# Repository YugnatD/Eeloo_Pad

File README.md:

# Eeloo Pad
## A Kerbal Space Program Control Panel
A Open Source project to create a control panel for Kerbal Space Program. The goal is to create a control panel that can be used to control the game from a physical panel. The control panel will be able to control the game, and display information about the game.

## Features
* Control the game (Thrust, SAS, RCS, etc.)
* TODO

## Block Diagram
[Diagram](https://app.diagrams.net/#G1_EMb1VFjsUEVt7AdRK-4kCuMEsyWomvp)

## Schematic

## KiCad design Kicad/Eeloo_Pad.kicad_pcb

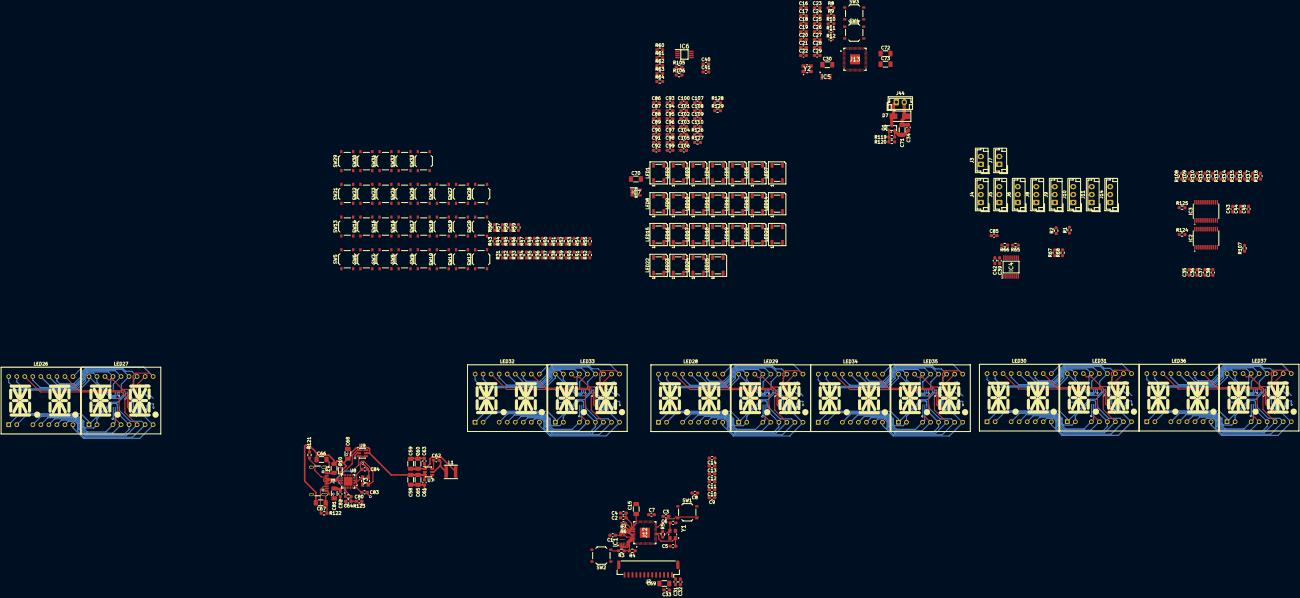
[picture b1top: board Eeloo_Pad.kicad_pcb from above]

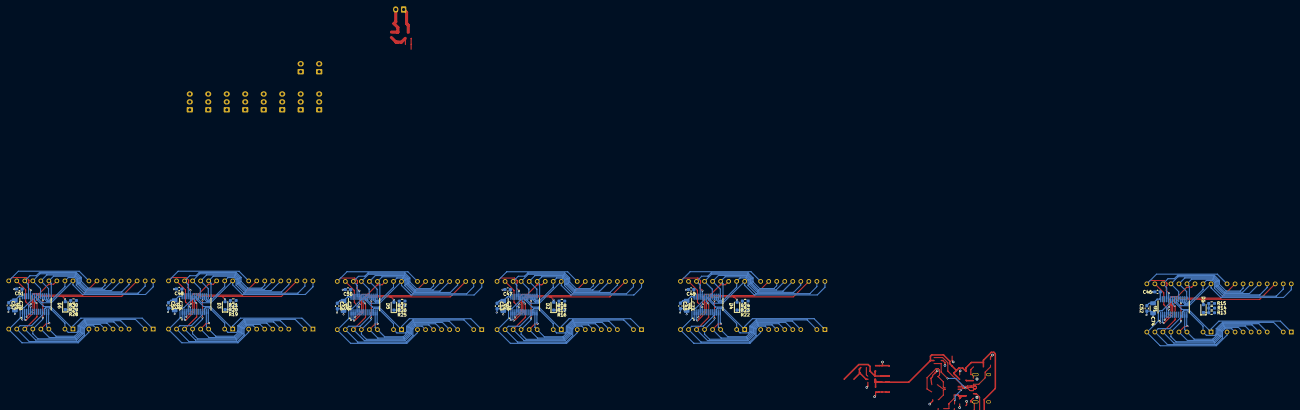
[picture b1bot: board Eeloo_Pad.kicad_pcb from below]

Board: 2 copper layers, 318 parts (48 on the bottom side), 265 nets.

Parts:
C1, C3, C4, C8, C9, C10, C11, C12, C13, C14, C16, C18, C19, C23, C24, C25, C26, C27, C28, C29, C31, C32, C33, C34, C35, C36, C37, C38, C39, C40, C41, C42, C43, C44, C45, C46, C47, C48, C49, C50, C51, C52, C53, C54, C55, C56, C57, C64, C82, C85, C86, C87, C88, C89, C90, C91, C92, C93, C94, C95, C96, C97, C98, C99, C100, C101, C102, C103, C104, C105, C106, C107, C108, C109, C110: 100n; C_0603_1608Metric_Pad1.08x0.95mm_HandSolder
C2, C7, C17, C22, C80: 1u; C_0603_1608Metric_Pad1.08x0.95mm_HandSolder
C5, C6, C20, C21, C83, C84: 15p; C_0603_1608Metric_Pad1.08x0.95mm_HandSolder
C15, C30, C81: 10u; C_1206_3216Metric_Pad1.33x1.80mm_HandSolder
C58, C59, C60, C65, C66, C67, C68, C69, C70, C71, C72, C73, C74, C75, C76, C77, C78, C79: 22uF; C_1206_3216Metric_Pad1.33x1.80mm_HandSolder
C61, C62, C63: 100nF; C_0603_1608Metric_Pad1.08x0.95mm_HandSolder
D1, D2, D3, D4, D5, D6: SD103AWS; D_SOD-323_HandSoldering
D7: SS34; D_SMA
D10: ESD5Zxx; D_SOD-523
F1: 1.5A; Fuse_1206_3216Metric
IC1, IC5: W25Q16JVUXIQ_TR; SON50P300X200X60-9N
IC2, IC3: PCA9535PW; TSSOP-24_4.4x7.8mm_P0.65mm
IC4: ADS7830IPWR; SOP65P640X120-16N
IC6: TCA9617ADGKR; SOP65P490X110-8N
IC7: SN74AHCT1G125DBVR; SOT95P280X145-5N
J1: USB_C_Receptacle_USB2.0_16P; USB_C_Receptacle_HCTL_HC-TYPE-C-16P-01A
J2: Conn_01x13; JST_GH_SM13B-GHS-TB_1x13-1MP_P1.25mm_Horizontal
J3, J7, J44: Conn_01x02_Pin; JST_EH_B2B-EH-A_1x02_P2.50mm_Vertical
J4, J5, J6, J8, J9, J10, J11, J14: Conn_01x03_Pin; JST_EH_B3B-EH-A_1x03_P2.50mm_Vertical
J12, J13: SC0914_13_; SC091413
L1: 3.9uH; L_Sunlord_SWPA4030S
LED1, LED2, LED3, LED4, LED5, LED6, LED7, LED8, LED9, LED10, LED11, LED12, LED13, LED14, LED15, LED16, LED17, LED18, LED19, LED20, LED21, LED22, LED23, LED24, LED25: XL-5050RGBC-WS2812B; LED_WS2812B_PLCC4_5.0x5.0mm_P3.2mm
LED26, LED27, LED28, LED29, LED30, LED31, LED32, LED33, LED34, LED35, LED36, LED37: FJ5241AH; LED-SEG-TH_18P-L25.2-W21.1-P2.54-LS15.2-BL
Q1: AO3400A; SOT-23
R1, R2, R31, R32, R33, R34, R35, R36, R37, R38, R39, R40, R41, R42, R43, R44, R45, R46, R47, R48, R49, R50, R51, R52, R53, R54, R55, R56, R57, R58, R59, R62, R65, R66, R67, R68, R107, R108, R109, R110, R111, R112, R113, R114, R115, R116, R117, R118, R119, R123, R124, R125, R127, R128, R129: 10k; R_0603_1608Metric_Pad0.98x0.95mm_HandSolder
R3, R5, R8, R10: 1k; R_0603_1608Metric_Pad0.98x0.95mm_HandSolder
R4, R9: NC; R_0603_1608Metric_Pad0.98x0.95mm_HandSolder
R6, R7, R11, R12: 27.4; R_0402_1005Metric_Pad0.72x0.64mm_HandSolder
R13, R14, R15, R16, R17, R18, R19, R20, R21, R22, R23, R24, R25, R26, R27, R28, R29, R30: 39k; R_0603_1608Metric_Pad0.98x0.95mm_HandSolder
R60, R61, R63, R64, R105, R106: 4k7; R_0603_1608Metric_Pad0.98x0.95mm_HandSolder
R120: 100; R_0603_1608Metric_Pad0.98x0.95mm_HandSolder
R121, R122: 5.1k; R_0603_1608Metric_Pad0.98x0.95mm_HandSolder
R126: 330; R_0603_1608Metric_Pad0.98x0.95mm_HandSolder
SW1, SW2, SW3, SW4, SW5, SW6, SW7, SW8, SW9, SW10, SW11, SW12, SW13, SW14, SW15, SW16, SW17, SW18, SW19, SW20, SW21, SW22, SW23, SW24, SW25, SW26, SW27, SW28, SW29, SW30, SW31, SW32, SW33: SW_Push; SW_Push_1P1T_XKB_TS-1187A
U1, U2, U3, U4, U5, U6: HT16K33A-28SSOP; SOP63P600X175-28N
U7: AP63203WU; TSOT-23-6
U8: CH334F; QFN-24-1EP_4x4mm_P0.5mm_EP2.7x2.7mm
U9: USBLC6-2SC6; SOT-23-6
Y1, Y2: ABM8-272-T3; ABM8272T3
Y3: 12MHz; ABM8272T3

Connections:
+3.3V: C1.1, C7.1, C8.1, C9.1, C10.1, C11.1, C12.1, C13.1, C14.1, C15.1, C16.1, C22.1, C23.1, C24.1, C25.1, C26.1, C27.1, C28.1, C29.1, C30.1, C31.1, C32.1, C33.1, C35.1, C36.1, C37.1, C38.1, C39.1, C40.1, C42.1, C59.1, C60.1, C63.1, C69.1, C72.1, C73.1, C85.1, IC1.8 (VCC), IC2.24 (VCC), IC3.24 (VCC), IC4.10 (REFIN/REFOUT), IC4.16 (+VDD), IC5.8 (VCC), IC6.1 (VCC(A)), J2.1, J4.1, J5.1, J6.1, J8.1, J9.1, J10.1, J11.1, J12.1 (IOVDD_1), J12.10 (IOVDD_2), J12.22 (IOVDD_3), J12.33 (IOVDD_4), J12.42 (IOVDD_5), J12.43 (ADC_AVDD), J12.44 (VREG_VIN), J12.48 (USB_VDD), J12.49 (IOVDD_6), J13.1 (IOVDD_1), J13.10 (IOVDD_2), J13.22 (IOVDD_3), J13.33 (IOVDD_4), J13.42 (IOVDD_5), J13.43 (ADC_AVDD), J13.44 (VREG_VIN), J13.48 (USB_VDD), J13.49 (IOVDD_6), J14.1, L1.2, R1.2, R2.2, R4.2, R9.2, R31.1, R32.1, R33.1, R34.1, R35.1, R36.1, R37.1, R38.1, R39.1, R40.1, R41.1, R42.1, R43.1, R44.1, R45.1, R46.1, R47.1, R48.1, R49.1, R50.1, R51.1, R52.1, R53.1, R54.1, R55.1, R56.1, R57.1, R58.1, R59.1, R63.1, R64.1, R65.1, R67.1, R105.1, R106.1, R107.1, R109.1, R111.1, R113.1, R115.1, R117.1, R124.1, R125.1, U7.1 (FB)
/CC1: J1.A5 (CC1), R121.1
/CC2: J1.B5 (CC2), R122.1
/HUB_OVCUR: R128.2, U8.1 (~OVCUR)
/HUB_PSELF: R129.1, U8.18 (PSELF)
/HUB_RESET: R123.2, U8.16 (~RESET/CDP)
/HUB_V33: C64.1, C80.1, R123.1, R128.1, U8.20 (VDD33_{LDO})
/USB1_DM: R7.2, U8.11 (DM1-)
/USB1_DP: R6.2, U8.12 (DP1+)
/USB2_DM: R12.2, U8.9 (DM2-)
/USB2_DP: R11.2, U8.10 (DP2+)
/USB_DM: J1.A7 (D-), J1.B7 (D-), U8.14 (DMU-), U9.1 (I/O1), U9.6 (I/O1)
/USB_DP: J1.A6 (D+), J1.B6 (D+), U8.15 (DPU+), U9.3 (I/O2), U9.4 (I/O2)
/VBUS: C34.1, C41.1, C43.1, C44.1, C45.1, C46.1, C47.1, C48.1, C49.1, C50.1, C51.1, C52.1, C53.1, C54.1, C55.1, C56.1, C57.1, C58.1, C61.1, C65.1, C66.1, C67.1, C68.1, C70.1, C71.1, C74.1, C75.1, C76.1, C77.1, C78.1, C79.1, C81.1, C82.1, C86.1, C87.1, C88.1, C89.1, C90.1, C91.1, C92.1, C93.1, C94.1, C95.1, C96.1, C97.1, C98.1, C99.1, C100.1, C101.1, C102.1, C103.1, C104.1, C105.1, C106.1, C107.1, C108.1, C109.1, C110.1, D7.1 (K), D10.1 (K), F1.2, IC6.8 (VCC(B)), IC7.5 (VCC), J44.2, LED1.1 (VDD), LED2.1 (VDD), LED3.1 (VDD), LED4.1 (VDD), LED5.1 (VDD), LED6.1 (VDD), LED7.1 (VDD), LED8.1 (VDD), LED9.1 (VDD), LED10.1 (VDD), LED11.1 (VDD), LED12.1 (VDD), LED13.1 (VDD), LED14.1 (VDD), LED15.1 (VDD), LED16.1 (VDD), LED17.1 (VDD), LED18.1 (VDD), LED19.1 (VDD), LED20.1 (VDD), LED21.1 (VDD), LED22.1 (VDD), LED23.1 (VDD), LED24.1 (VDD), LED25.1 (VDD), R60.1, R61.1, R62.1, U1.28 (VDD), U2.28 (VDD), U3.28 (VDD), U4.28 (VDD), U5.28 (VDD), U6.28 (VDD), U7.2 (EN), U7.3 (IN), U8.19 (V5), U9.5 (VBUS)
/control_module/ANTINORMAL: IC3.7 (P03), R49.2, SW21.2
/control_module/ANTI_MANEUVER: IC3.14 (P11), R55.2, SW32.2
/control_module/ANTI_TARGET: IC3.11 (P07), R53.2, SW28.2
/control_module/BRAKE: IC2.19 (P16), R45.2, SW19.2
/control_module/CIBLE_ORBIT: IC3.15 (P12), R56.2, SW31.2
/control_module/CTRL0: IC2.6 (P02), R33.2, SW7.2
/control_module/CTRL1: IC2.7 (P03), R34.2, SW8.2
/control_module/CTRL2: IC2.8 (P04), R35.2, SW9.2
/control_module/CTRL3: IC2.9 (P05), R36.2, SW14.2
/control_module/CTRL4: IC2.10 (P06), R37.2, SW13.2
/control_module/CTRL5: IC2.11 (P07), R38.2, SW12.2
/control_module/CTRL6: IC2.13 (P10), R39.2, SW11.2
/control_module/CTRL7: IC2.14 (P11), R40.2, SW10.2
/control_module/CTRL8: IC2.15 (P12), R41.2, SW15.2
/control_module/CTRL9: IC2.16 (P13), R42.2, SW16.2
/control_module/EXT1: IC4.1 (CH0), J14.2
/control_module/GEAR: IC2.18 (P15), R44.2, SW18.2
/control_module/I2C0_SCL_33: IC2.22 (SCL), IC3.22 (SCL), IC4.14 (SCL), J13.7 (GPIO5), R105.2
/control_module/I2C0_SDA_33: IC2.23 (SDA), IC3.23 (SDA), IC4.15 (SDA), J13.6 (GPIO4), R106.2
/control_module/I2C1_SCL_33: IC6.2 (SCLA), J13.14 (GPIO11), R63.2
/control_module/I2C1_SCL_50: IC6.7 (SCLB), R60.2, U1.26 (SCL), U2.26 (SCL), U3.26 (SCL), U4.26 (SCL), U5.26 (SCL), U6.26 (SCL)
/control_module/I2C1_SDA_33: IC6.3 (SDAA), J13.13 (GPIO10), R64.2
/control_module/I2C1_SDA_50: IC6.6 (SDAB), R61.2, U1.27 (SDA), U2.27 (SDA), U3.27 (SDA), U4.27 (SDA), U5.27 (SDA), U6.27 (SDA)
/control_module/I2C_GPIO_EXT0_INT: IC2.1 (~INT), J13.18 (GPIO15), R124.2
/control_module/I2C_GPIO_EXT1_INT: IC3.1 (~INT), J13.27 (GPIO16), R125.2
/control_module/JOY_BTN_D: IC3.18 (P15), J7.1, R2.1
/control_module/JOY_BTN_G: IC3.19 (P16), J3.1, R1.1
/control_module/JOY_D_AXIS_R: IC4.3 (CH2), J10.2
/control_module/JOY_D_AXIS_X: IC4.5 (CH4), J8.2
/control_module/JOY_D_AXIS_Y: IC4.4 (CH3), J9.2
/control_module/JOY_G_AXIS_R: IC4.6 (CH5), J6.2
/control_module/JOY_G_AXIS_X: IC4.8 (CH7), J4.2
/control_module/JOY_G_AXIS_Y: IC4.7 (CH6), J5.2
/control_module/LED_CTRL_33: IC7.2 (A), J13.32 (GPIO21), R127.1
/control_module/LED_CTRL_50: IC7.4 (Y), R126.2
/control_module/LIGHT: IC2.17 (P14), R43.2, SW17.2
/control_module/MANEUVER: IC3.13 (P10), R54.2, SW33.2
/control_module/NORMAL: IC3.6 (P02), R48.2, SW22.2
/control_module/ORBIT_SURFACE: IC3.16 (P13), R57.2, SW30.2
/control_module/PROGRADE: IC3.4 (P00), R46.2, SW24.2
/control_module/RADIAL_IN: IC3.8 (P04), R50.2, SW25.2
/control_module/RADIAL_OUT: IC3.9 (P05), R51.2, SW26.2
/control_module/RCS: IC2.5 (P01), R32.2, SW6.2
/control_module/RETROGRADE: IC3.5 (P01), R47.2, SW23.2
/control_module/SAS: IC2.4 (P00), R31.2, SW5.2
/control_module/SEA_EARTH: IC3.17 (P14), R58.2, SW29.2
/control_module/STAGE: IC2.20 (P17), R59.2, SW20.2
/control_module/TARGET: IC3.10 (P06), R52.2, SW27.2
/control_module/THROTTLE: IC4.2 (CH1), J11.2
/control_module/VIBRO_CTRL_33: J13.17 (GPIO14), R120.1
/control_module/seg_4x14_module1/A: LED32.12 (A), LED33.12 (A), U4.25 (ROW0/A2)
/control_module/seg_4x14_module1/A0: LED32.9 (C), LED33.9 (C), R22.1, U4.23 (ROW2/A0)
/control_module/seg_4x14_module1/A1: LED32.10 (B), LED33.10 (B), U4.24 (ROW1/A1)
/control_module/seg_4x14_module1/AD: D4.2 (A), LED32.16 (DIG1), U4.2 (COM0/AD)
/control_module/seg_4x14_module1/COM1: LED32.11 (DIG2), U4.3 (COM1/KS0)
/control_module/seg_4x14_module1/COM2: LED33.16 (DIG1), U4.4 (COM2/KS1)
/control_module/seg_4x14_module1/COM3: LED33.11 (DIG2), U4.5 (COM3/KS2)
/control_module/seg_4x14_module1/D: LED32.7 (D), LED33.7 (D), U4.22 (ROW3/K1)
/control_module/seg_4x14_module1/DP: LED32.8 (DP), LED33.8 (DP), U4.11 (ROW14/K12)
/control_module/seg_4x14_module1/E: LED32.1 (E), LED33.1 (E), U4.21 (ROW4/K2)
/control_module/seg_4x14_module1/F: LED32.18 (F), LED33.18 (F), U4.20 (ROW5/K3)
/control_module/seg_4x14_module1/G1: LED32.13 (G1), LED33.13 (G1), U4.19 (ROW6/K4)
/control_module/seg_4x14_module1/G2: LED32.6 (G2), LED33.6 (G2), U4.18 (ROW7/K5)
/control_module/seg_4x14_module1/H: LED32.17 (H), LED33.17 (H), U4.17 (ROW8/K6)
/control_module/seg_4x14_module1/J: LED32.15 (J), LED33.15 (J), U4.16 (ROW9/K7)
/control_module/seg_4x14_module1/K: LED32.14 (K), LED33.14 (K), U4.15 (ROW10/K8)
/control_module/seg_4x14_module1/L: LED32.5 (L), LED33.5 (L), U4.14 (ROW11/K9)
/control_module/seg_4x14_module1/M: LED32.4 (M), LED33.4 (M), U4.13 (ROW12/K10)
/control_module/seg_4x14_module1/N: LED32.2 (N), LED33.2 (N), U4.12 (ROW13/K11)
/control_module/seg_4x14_module2/A: LED34.12 (A), LED35.12 (A), U5.25 (ROW0/A2)
/control_module/seg_4x14_module2/A0: LED34.9 (C), LED35.9 (C), U5.23 (ROW2/A0)
/control_module/seg_4x14_module2/A1: LED34.10 (B), LED35.10 (B), R26.1, U5.24 (ROW1/A1)
/control_module/seg_4x14_module2/AD: D5.2 (A), LED34.16 (DIG1), U5.2 (COM0/AD)
/control_module/seg_4x14_module2/COM1: LED34.11 (DIG2), U5.3 (COM1/KS0)
/control_module/seg_4x14_module2/COM2: LED35.16 (DIG1), U5.4 (COM2/KS1)
/control_module/seg_4x14_module2/COM3: LED35.11 (DIG2), U5.5 (COM3/KS2)
/control_module/seg_4x14_module2/D: LED34.7 (D), LED35.7 (D), U5.22 (ROW3/K1)
/control_module/seg_4x14_module2/DP: LED34.8 (DP), LED35.8 (DP), U5.11 (ROW14/K12)
/control_module/seg_4x14_module2/E: LED34.1 (E), LED35.1 (E), U5.21 (ROW4/K2)
/control_module/seg_4x14_module2/F: LED34.18 (F), LED35.18 (F), U5.20 (ROW5/K3)
/control_module/seg_4x14_module2/G1: LED34.13 (G1), LED35.13 (G1), U5.19 (ROW6/K4)
/control_module/seg_4x14_module2/G2: LED34.6 (G2), LED35.6 (G2), U5.18 (ROW7/K5)
/control_module/seg_4x14_module2/H: LED34.17 (H), LED35.17 (H), U5.17 (ROW8/K6)
/control_module/seg_4x14_module2/J: LED34.15 (J), LED35.15 (J), U5.16 (ROW9/K7)
/control_module/seg_4x14_module2/K: LED34.14 (K), LED35.14 (K), U5.15 (ROW10/K8)
/control_module/seg_4x14_module2/L: LED34.5 (L), LED35.5 (L), U5.14 (ROW11/K9)
/control_module/seg_4x14_module2/M: LED34.4 (M), LED35.4 (M), U5.13 (ROW12/K10)
/control_module/seg_4x14_module2/N: LED34.2 (N), LED35.2 (N), U5.12 (ROW13/K11)
/control_module/seg_4x14_module3/A: LED28.12 (A), LED29.12 (A), U2.25 (ROW0/A2)
/control_module/seg_4x14_module3/A0: LED28.9 (C), LED29.9 (C), R16.1, U2.23 (ROW2/A0)
/control_module/seg_4x14_module3/A1: LED28.10 (B), LED29.10 (B), R17.1, U2.24 (ROW1/A1)
/control_module/seg_4x14_module3/AD: D2.2 (A), LED28.16 (DIG1), U2.2 (COM0/AD)
/control_module/seg_4x14_module3/COM1: LED28.11 (DIG2), U2.3 (COM1/KS0)
/control_module/seg_4x14_module3/COM2: LED29.16 (DIG1), U2.4 (COM2/KS1)
/control_module/seg_4x14_module3/COM3: LED29.11 (DIG2), U2.5 (COM3/KS2)
/control_module/seg_4x14_module3/D: LED28.7 (D), LED29.7 (D), U2.22 (ROW3/K1)
/control_module/seg_4x14_module3/DP: LED28.8 (DP), LED29.8 (DP), U2.11 (ROW14/K12)
/control_module/seg_4x14_module3/E: LED28.1 (E), LED29.1 (E), U2.21 (ROW4/K2)
/control_module/seg_4x14_module3/F: LED28.18 (F), LED29.18 (F), U2.20 (ROW5/K3)
/control_module/seg_4x14_module3/G1: LED28.13 (G1), LED29.13 (G1), U2.19 (ROW6/K4)
/control_module/seg_4x14_module3/G2: LED28.6 (G2), LED29.6 (G2), U2.18 (ROW7/K5)
/control_module/seg_4x14_module3/H: LED28.17 (H), LED29.17 (H), U2.17 (ROW8/K6)
/control_module/seg_4x14_module3/J: LED28.15 (J), LED29.15 (J), U2.16 (ROW9/K7)
/control_module/seg_4x14_module3/K: LED28.14 (K), LED29.14 (K), U2.15 (ROW10/K8)
/control_module/seg_4x14_module3/L: LED28.5 (L), LED29.5 (L), U2.14 (ROW11/K9)
/control_module/seg_4x14_module3/M: LED28.4 (M), LED29.4 (M), U2.13 (ROW12/K10)
/control_module/seg_4x14_module3/N: LED28.2 (N), LED29.2 (N), U2.12 (ROW13/K11)
/control_module/seg_4x14_module4/A: LED30.12 (A), LED31.12 (A), R21.1, U3.25 (ROW0/A2)
/control_module/seg_4x14_module4/A0: LED30.9 (C), LED31.9 (C), U3.23 (ROW2/A0)
/control_module/seg_4x14_module4/A1: LED30.10 (B), LED31.10 (B), U3.24 (ROW1/A1)
/control_module/seg_4x14_module4/AD: D3.2 (A), LED30.16 (DIG1), U3.2 (COM0/AD)
/control_module/seg_4x14_module4/COM1: LED30.11 (DIG2), U3.3 (COM1/KS0)
/control_module/seg_4x14_module4/COM2: LED31.16 (DIG1), U3.4 (COM2/KS1)
/control_module/seg_4x14_module4/COM3: LED31.11 (DIG2), U3.5 (COM3/KS2)
/control_module/seg_4x14_module4/D: LED30.7 (D), LED31.7 (D), U3.22 (ROW3/K1)
/control_module/seg_4x14_module4/DP: LED30.8 (DP), LED31.8 (DP), U3.11 (ROW14/K12)
/control_module/seg_4x14_module4/E: LED30.1 (E), LED31.1 (E), U3.21 (ROW4/K2)
/control_module/seg_4x14_module4/F: LED30.18 (F), LED31.18 (F), U3.20 (ROW5/K3)
/control_module/seg_4x14_module4/G1: LED30.13 (G1), LED31.13 (G1), U3.19 (ROW6/K4)
/control_module/seg_4x14_module4/G2: LED30.6 (G2), LED31.6 (G2), U3.18 (ROW7/K5)
/control_module/seg_4x14_module4/H: LED30.17 (H), LED31.17 (H), U3.17 (ROW8/K6)
/control_module/seg_4x14_module4/J: LED30.15 (J), LED31.15 (J), U3.16 (ROW9/K7)
/control_module/seg_4x14_module4/K: LED30.14 (K), LED31.14 (K), U3.15 (ROW10/K8)
/control_module/seg_4x14_module4/L: LED30.5 (L), LED31.5 (L), U3.14 (ROW11/K9)
/control_module/seg_4x14_module4/M: LED30.4 (M), LED31.4 (M), U3.13 (ROW12/K10)
/control_module/seg_4x14_module4/N: LED30.2 (N), LED31.2 (N), U3.12 (ROW13/K11)
/control_module/seg_4x14_module5/A: LED36.12 (A), LED37.12 (A), R30.1, U6.25 (ROW0/A2)
/control_module/seg_4x14_module5/A0: LED36.9 (C), LED37.9 (C), R28.1, U6.23 (ROW2/A0)
/control_module/seg_4x14_module5/A1: LED36.10 (B), LED37.10 (B), U6.24 (ROW1/A1)
/control_module/seg_4x14_module5/AD: D6.2 (A), LED36.16 (DIG1), U6.2 (COM0/AD)
/control_module/seg_4x14_module5/COM1: LED36.11 (DIG2), U6.3 (COM1/KS0)
/control_module/seg_4x14_module5/COM2: LED37.16 (DIG1), U6.4 (COM2/KS1)
/control_module/seg_4x14_module5/COM3: LED37.11 (DIG2), U6.5 (COM3/KS2)
/control_module/seg_4x14_module5/D: LED36.7 (D), LED37.7 (D), U6.22 (ROW3/K1)
/control_module/seg_4x14_module5/DP: LED36.8 (DP), LED37.8 (DP), U6.11 (ROW14/K12)
/control_module/seg_4x14_module5/E: LED36.1 (E), LED37.1 (E), U6.21 (ROW4/K2)
/control_module/seg_4x14_module5/F: LED36.18 (F), LED37.18 (F), U6.20 (ROW5/K3)
/control_module/seg_4x14_module5/G1: LED36.13 (G1), LED37.13 (G1), U6.19 (ROW6/K4)
/control_module/seg_4x14_module5/G2: LED36.6 (G2), LED37.6 (G2), U6.18 (ROW7/K5)
/control_module/seg_4x14_module5/H: LED36.17 (H), LED37.17 (H), U6.17 (ROW8/K6)
/control_module/seg_4x14_module5/J: LED36.15 (J), LED37.15 (J), U6.16 (ROW9/K7)
/control_module/seg_4x14_module5/K: LED36.14 (K), LED37.14 (K), U6.15 (ROW10/K8)
/control_module/seg_4x14_module5/L: LED36.5 (L), LED37.5 (L), U6.14 (ROW11/K9)
/control_module/seg_4x14_module5/M: LED36.4 (M), LED37.4 (M), U6.13 (ROW12/K10)
/control_module/seg_4x14_module5/N: LED36.2 (N), LED37.2 (N), U6.12 (ROW13/K11)
/control_module/seg_4x14_module/A: LED26.12 (A), LED27.12 (A), U1.25 (ROW0/A2)
/control_module/seg_4x14_module/A0: LED26.9 (C), LED27.9 (C), U1.23 (ROW2/A0)
/control_module/seg_4x14_module/A1: LED26.10 (B), LED27.10 (B), U1.24 (ROW1/A1)
/control_module/seg_4x14_module/AD: D1.2 (A), LED26.16 (DIG1), U1.2 (COM0/AD)
/control_module/seg_4x14_module/COM1: LED26.11 (DIG2), U1.3 (COM1/KS0)
/control_module/seg_4x14_module/COM2: LED27.16 (DIG1), U1.4 (COM2/KS1)
/control_module/seg_4x14_module/COM3: LED27.11 (DIG2), U1.5 (COM3/KS2)
/control_module/seg_4x14_module/D: LED26.7 (D), LED27.7 (D), U1.22 (ROW3/K1)
/control_module/seg_4x14_module/DP: LED26.8 (DP), LED27.8 (DP), U1.11 (ROW14/K12)
/control_module/seg_4x14_module/E: LED26.1 (E), LED27.1 (E), U1.21 (ROW4/K2)
/control_module/seg_4x14_module/F: LED26.18 (F), LED27.18 (F), U1.20 (ROW5/K3)
/control_module/seg_4x14_module/G1: LED26.13 (G1), LED27.13 (G1), U1.19 (ROW6/K4)
/control_module/seg_4x14_module/G2: LED26.6 (G2), LED27.6 (G2), U1.18 (ROW7/K5)
/control_module/seg_4x14_module/H: LED26.17 (H), LED27.17 (H), U1.17 (ROW8/K6)
/control_module/seg_4x14_module/J: LED26.15 (J), LED27.15 (J), U1.16 (ROW9/K7)
/control_module/seg_4x14_module/K: LED26.14 (K), LED27.14 (K), U1.15 (ROW10/K8)
/control_module/seg_4x14_module/L: LED26.5 (L), LED27.5 (L), U1.14 (ROW11/K9)
/control_module/seg_4x14_module/M: LED26.4 (M), LED27.4 (M), U1.13 (ROW12/K10)
/control_module/seg_4x14_module/N: LED26.2 (N), LED27.2 (N), U1.12 (ROW13/K11)
/control_module/uC1/+1.1V: C17.1, C18.1, C19.1, J13.23 (DVDD_1), J13.45 (VREG_VOUT), J13.50 (DVDD_2)
/control_module/uC1/QSPI_SCLK: IC5.6 (CLK), J13.52 (QSPI_SCLK)
/control_module/uC1/QSPI_SD0: IC5.5 (DI(IO0)), J13.53 (QSPI_SD0)
/control_module/uC1/QSPI_SD1: IC5.2 (DO(IO1)), J13.55 (QSPI_SD1)
/control_module/uC1/QSPI_SD2: IC5.3 (IO2), J13.54 (QSPI_SD2)
/control_module/uC1/QSPI_SD3: IC5.7 (IO3), J13.51 (QSPI_SD3)
/control_module/uC1/QSPI_SS: IC5.1 (~CS), J13.56 (QSPI_SS_N), R8.1, R9.1
/control_module/uC1/RUN: J13.26 (RUN), SW3.2
/control_module/uC1/XIN: C20.2, J13.20 (XIN), Y2.1
/control_module/uC1/XOUT: J13.21 (XOUT), R10.2
/navball_module/LCD_BL: J2.9, J12.37 (GPIO25)
/navball_module/LCD_CS: J2.6, J12.12 (GPIO9)
/navball_module/LCD_DC: J2.7, J12.11 (GPIO8)
/navball_module/LCD_RST: J2.8, J12.16 (GPIO13)
/navball_module/MISO: J2.3, J12.15 (GPIO12)
/navball_module/MOSI: J2.4, J12.14 (GPIO11)
/navball_module/SCLK: J2.5, J12.13 (GPIO10)
/navball_module/TP_INT: J2.12, J12.32 (GPIO21)
/navball_module/TP_RST: J2.13, J12.34 (GPIO22)
/navball_module/TP_SCL: J2.11, J12.9 (GPIO7)
/navball_module/TP_SDA: J2.10, J12.8 (GPIO6)
/navball_module/uC1/+1.1V: C2.1, C3.1, C4.1, J12.23 (DVDD_1), J12.45 (VREG_VOUT), J12.50 (DVDD_2)
/navball_module/uC1/QSPI_SCLK: IC1.6 (CLK), J12.52 (QSPI_SCLK)
/navball_module/uC1/QSPI_SD0: IC1.5 (DI(IO0)), J12.53 (QSPI_SD0)
/navball_module/uC1/QSPI_SD1: IC1.2 (DO(IO1)), J12.55 (QSPI_SD1)
/navball_module/uC1/QSPI_SD2: IC1.3 (IO2), J12.54 (QSPI_SD2)
/navball_module/uC1/QSPI_SD3: IC1.7 (IO3), J12.51 (QSPI_SD3)
/navball_module/uC1/QSPI_SS: IC1.1 (~CS), J12.56 (QSPI_SS_N), R3.1, R4.1
/navball_module/uC1/RUN: J12.26 (RUN), SW1.2
/navball_module/uC1/XIN: C5.2, J12.20 (XIN), Y1.1
/navball_module/uC1/XOUT: J12.21 (XOUT), R5.2
GND: C1.2, C2.2, C3.2, C4.2, C5.1, C6.1, C7.2, C8.2, C9.2, C10.2, C11.2, C12.2, C13.2, C14.2, C15.2, C16.2, C17.2, C18.2, C19.2, C20.1, C21.1, C22.2, C23.2, C24.2, C25.2, C26.2, C27.2, C28.2, C29.2, C30.2, C31.2, C32.2, C33.2, C34.2, C35.2, C36.2, C37.2, C38.2, C39.2, C40.2, C41.2, C42.2, C43.2, C44.2, C45.2, C46.2, C47.2, C48.2, C49.2, C50.2, C51.2, C52.2, C53.2, C54.2, C55.2, C56.2, C57.2, C58.2, C59.2, C60.2, C61.2, C63.2, C64.2, C65.2, C66.2, C67.2, C68.2, C69.2, C70.2, C71.2, C72.2, C73.2, C74.2, C75.2, C76.2, C77.2, C78.2, C79.2, C80.2, C81.2, C82.2, C83.1, C84.1, C85.2, C86.2, C87.2, C88.2, C89.2, C90.2, C91.2, C92.2, C93.2, C94.2, C95.2, C96.2, C97.2, C98.2, C99.2, C100.2, C101.2, C102.2, C103.2, C104.2, C105.2, C106.2, C107.2, C108.2, C109.2, C110.2, D10.2 (A), IC1.4 (GND), IC1.9 (EP), IC2.12 (GND), IC3.12 (GND), IC4.9 (GND), IC4.11 (COM), IC5.4 (GND), IC5.9 (EP), IC6.4 (GND), IC7.1 (~OE), IC7.3 (GND), J1.A1 (GND), J1.A12 (GND), J1.B1 (GND), J1.B12 (GND), J1.S1 (SHIELD), J2.2, J3.2, J4.3, J5.3, J6.3, J7.2, J8.3, J9.3, J10.3, J11.3, J12.19 (TESTEN), J12.57 (GND), J13.19 (TESTEN), J13.57 (GND), J14.3, LED1.3 (GND), LED2.3 (GND), LED3.3 (GND), LED4.3 (GND), LED5.3 (GND), LED6.3 (GND), LED7.3 (GND), LED8.3 (GND), LED9.3 (GND), LED10.3 (GND), LED11.3 (GND), LED12.3 (GND), LED13.3 (GND), LED14.3 (GND), LED15.3 (GND), LED16.3 (GND), LED17.3 (GND), LED18.3 (GND), LED19.3 (GND), LED20.3 (GND), LED21.3 (GND), LED22.3 (GND), LED23.3 (GND), LED24.3 (GND), LED25.3 (GND), Q1.2 (S), R66.2, R68.2, R108.2, R110.2, R112.2, R114.2, R116.2, R118.2, R119.2, R121.2, R122.2, R127.2, R129.2, SW1.1, SW2.1, SW3.1, SW4.1, SW5.1, SW6.1, SW7.1, SW8.1, SW9.1, SW10.1, SW11.1, SW12.1, SW13.1, SW14.1, SW15.1, SW16.1, SW17.1, SW18.1, SW19.1, SW20.1, SW21.1, SW22.1, SW23.1, SW24.1, SW25.1, SW26.1, SW27.1, SW28.1, SW29.1, SW30.1, SW31.1, SW32.1, SW33.1, U1.1 (VSS), U2.1 (VSS), U3.1 (VSS), U4.1 (VSS), U5.1 (VSS), U6.1 (VSS), U7.4 (GND), U8.25 (GND), U9.2 (GND), Y1.2, Y1.4, Y2.2, Y2.4, Y3.2 (G), Y3.4 (G)
unnamed: C6.2, R5.1, Y1.3
unnamed: C21.2, R10.1, Y2.3
unnamed: D1.1 (K), R13.2, R14.2, R15.2
unnamed: D2.1 (K), R16.2, R17.2, R18.2
unnamed: D3.1 (K), R19.2, R20.2, R21.2
unnamed: D4.1 (K), R22.2, R23.2, R24.2
unnamed: D5.1 (K), R25.2, R26.2, R27.2
unnamed: D6.1 (K), R28.2, R29.2, R30.2
unnamed: D7.2 (A), J44.1, Q1.3 (D)
unnamed: F1.1, J1.A4 (VBUS), J1.A9 (VBUS), J1.B4 (VBUS), J1.B9 (VBUS)
unnamed: IC2.21 (A0), R107.2, R108.1
unnamed: IC2.2 (A1), R109.2, R110.1
unnamed: IC2.3 (A2), R111.2, R112.1
unnamed: IC3.21 (A0), R113.2, R114.1
unnamed: IC3.2 (A1), R115.2, R116.1
unnamed: IC3.3 (A2), R117.2, R118.1
unnamed: IC4.12 (A0), R67.2, R68.1
unnamed: IC4.13 (A1), R65.2, R66.1
unnamed: IC6.5 (EN), R62.2
unnamed: J12.46 (USB_DM), R7.1
unnamed: J12.47 (USB_DP), R6.1
unnamed: J13.46 (USB_DM), R12.1
unnamed: J13.47 (USB_DP), R11.1
unnamed: LED1.4 (DIN), R126.1
unnamed: LED1.2 (DOU), LED6.4 (DIN)
unnamed: LED2.4 (DIN), LED21.2 (DOU)
unnamed: LED2.2 (DOU), LED7.4 (DIN)
unnamed: LED3.2 (DOU), LED8.4 (DIN)
unnamed: LED4.2 (DOU), LED9.4 (DIN)
unnamed: LED5.2 (DOU), LED10.4 (DIN)
unnamed: LED10.2 (DOU), LED15.4 (DIN)
unnamed: LED6.2 (DOU), LED11.4 (DIN)
unnamed: LED11.2 (DOU), LED16.4 (DIN)
unnamed: LED7.2 (DOU), LED12.4 (DIN)
unnamed: LED12.2 (DOU), LED17.4 (DIN)
unnamed: LED8.2 (DOU), LED13.4 (DIN)
unnamed: LED13.2 (DOU), LED18.4 (DIN)
unnamed: LED9.2 (DOU), LED14.4 (DIN)
unnamed: LED14.2 (DOU), LED19.4 (DIN)
unnamed: LED15.2 (DOU), LED20.4 (DIN)
unnamed: LED16.2 (DOU), LED21.4 (DIN)
unnamed: LED17.2 (DOU), LED22.4 (DIN)
unnamed: LED18.2 (DOU), LED23.4 (DIN)
unnamed: LED19.2 (DOU), LED24.4 (DIN)
unnamed: LED20.2 (DOU), LED25.4 (DIN)
unnamed: LED3.4 (DIN), LED22.2 (DOU)
unnamed: LED4.4 (DIN), LED23.2 (DOU)
unnamed: LED5.4 (DIN), LED24.2 (DOU)
unnamed: Q1.1 (G), R119.1, R120.2
unnamed: R3.2, SW2.2
unnamed: R8.2, SW4.2
unnamed: C62.1, U7.6 (BST)
unnamed: C62.2, L1.1, U7.5 (SW)
unnamed: C84.2, U8.4 (XI), Y3.3
unnamed: C83.2, U8.3 (XO), Y3.1

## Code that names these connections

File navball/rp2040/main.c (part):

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#define PIN_LCD_SCK   10
#define PIN_LCD_MOSI  11
#define PIN_LCD_MISO  12
#define PIN_LCD_CS     9

#define PIN_LCD_DC     8
#define PIN_LCD_RST   13
#define PIN_LCD_BL    25

#define SPI_PORT spi1

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

// --- Low-level LCD helpers (GC9A01A) ---
static inline void cs_select()   { gpio_put(PIN_LCD_CS, 0); }
static inline void cs_deselect() { gpio_put(PIN_LCD_CS, 1); }
static inline void dc_command()  { gpio_put(PIN_LCD_DC, 0); }
static inline void dc_data()     { gpio_put(PIN_LCD_DC, 1); }



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}

static void lcd_reset(void) {
    gpio_put(PIN_LCD_RST, 0); sleep_ms(50);
    gpio_put(PIN_LCD_RST, 1); sleep_ms(120);
}

// Parser that sends each {cmd, len, [data...] | delay}
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    gpio_set_function(PIN_LCD_SCK,  GPIO_FUNC_SPI);
    gpio_set_function(PIN_LCD_MOSI, GPIO_FUNC_SPI);
    // CS / DC / RST / BL as GPIO
    gpio_init(PIN_LCD_CS);  gpio_set_dir(PIN_LCD_CS, GPIO_OUT);  gpio_put(PIN_LCD_CS, 1);
    gpio_init(PIN_LCD_DC);  gpio_set_dir(PIN_LCD_DC, GPIO_OUT);  gpio_put(PIN_LCD_DC, 1);
    gpio_init(PIN_LCD_RST); gpio_set_dir(PIN_LCD_RST, GPIO_OUT); gpio_put(PIN_LCD_RST, 1);
    gpio_init(PIN_LCD_BL);  gpio_set_dir(PIN_LCD_BL, GPIO_OUT);  gpio_put(PIN_LCD_BL, 1); // backlight on
    gpio_init(PIN_LCD_MISO); gpio_set_dir(PIN_LCD_MISO, GPIO_IN);

    lcd_init();
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
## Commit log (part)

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2023-03-10 Adding empty BOM and modification of the README
2023-03-10 Adding link to Block Diagram
2023-03-14 Adding a template for the communication mod
2023-03-14 Adding Project for KSP1
2023-03-15 Modification of the structure
2023-03-15 Print working without crash
2023-03-15 Adding Socket template for communication
2023-03-15 Casting data seem to work
2023-03-15 Reading XML + Better managing of the socket
2023-03-16 Can control the SAS through socket + Disabling the timer when not in flight
2023-03-16 Adding attribute to structure
2023-03-16 Tried adding more attribut
2023-03-17 Decoding of the vesselPacket seem to work
2023-03-17 Getting data and control with python from the socket seems to work
2023-03-17 Adding comment
2023-03-17 Some CleanUp for the Python
2023-03-17 Minor timing correction + remove Debug.Log
2023-04-04 Tried something for the navball
2023-04-05 Working on the C version for the navball
2023-04-06 Added more function for navball in C
2023-04-06 Navball close to working version in C
2023-04-20 Good value, but the result is not correct
2023-07-07 working c version to generate navball
2023-07-08 Modification to make computation on the stack for uC usage, need some optimisation
2023-07-08 Some optimisation
2023-07-08 Optimisation and adding yaw
2023-07-08 now everything is on stack, and the texture is stored on a c file
2023-07-08 tried to run navball on lpc54s018
2023-07-08 Really Optimised version
2023-07-09 Navball Working on LPC
2023-07-15 Tried to optimise
2023-10-11 adding last file from my pc
2023-10-11 Started to write a code in fixed point
2023-12-07 precalculed sin/cos
2023-12-23 adding formula
2023-12-25 some optimisation + writing of a mt version
2024-08-05 working version with precomputed value
2024-08-05 some cleanup
2024-08-08 minor correction on fastsin and fastcos
2025-11-23 working on the code to render navball
2025-11-30 working single core version using DMA, need to optimize and maybe paralelise this
2025-11-30 making the render multicore
2025-12-07 working on the schematics
2025-12-07 adding multiple component (14 semgent and led)
2025-12-08 working on the 14 segment schematics
